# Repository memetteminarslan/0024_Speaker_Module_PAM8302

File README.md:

# 0024_Speaker_Module_PAM8302
You are seeing a large number of widely used Speaker Module in electronic development kits. More information coming soon...

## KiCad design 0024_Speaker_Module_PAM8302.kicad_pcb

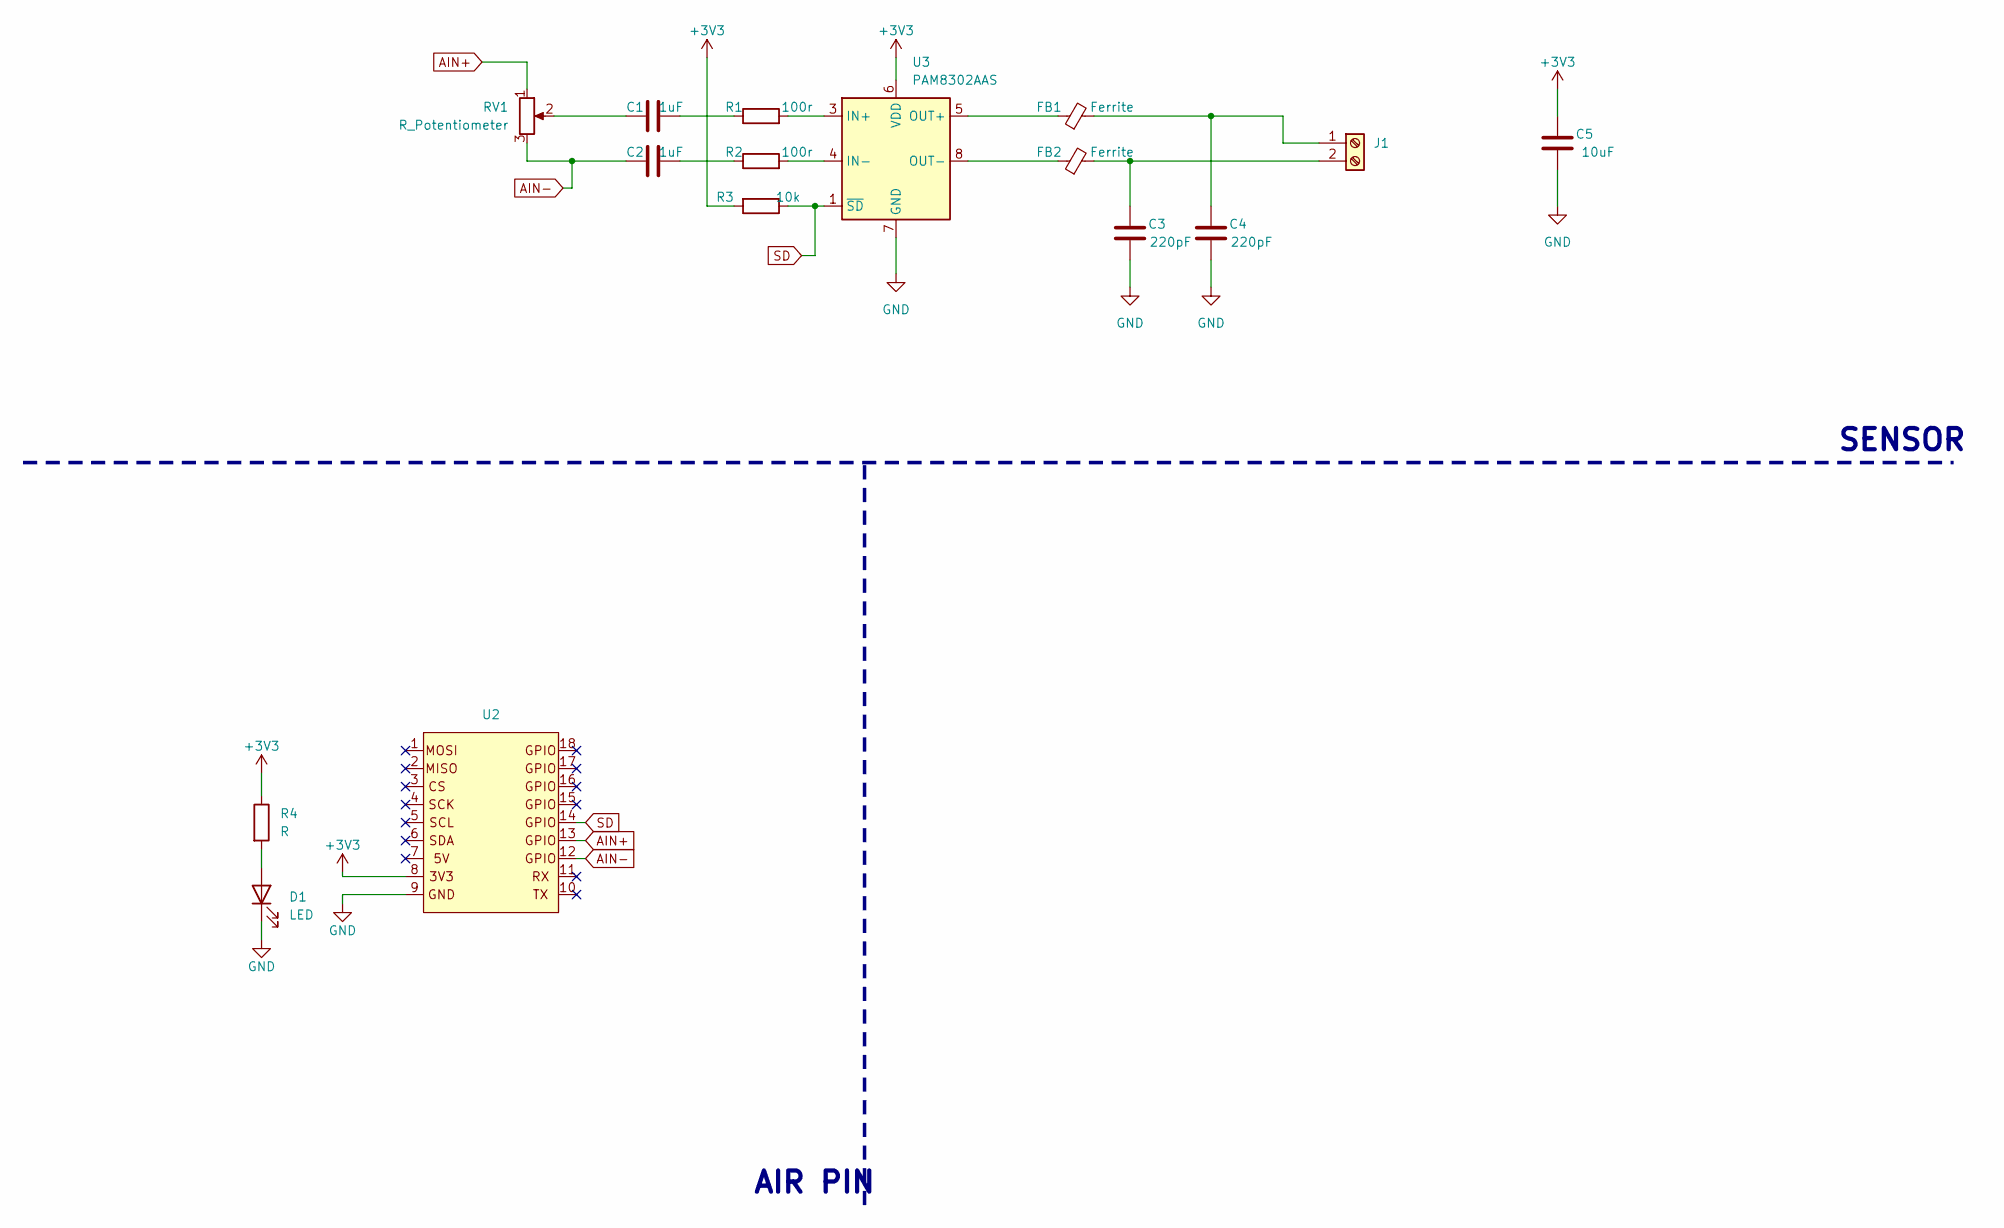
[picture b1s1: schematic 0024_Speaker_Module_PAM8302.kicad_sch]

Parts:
C1, C2: 1uF; C_0805_2012Metric
C3, C4: 220pF; C_0805_2012Metric
C5: 10uF; C_0603_1608Metric
D1: LED; LED_0805_2012Metric
FB1, FB2: Ferrite; L_0805_2012Metric
J1: Screw_Terminal_01x02; TerminalBlock_Phoenix_MKDS-1,5-2-5.08_1x02_P5.08mm_Horizont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
R1, R2: 100r; R_0805_2012Metric
R3: 10k; R_0805_2012Metric
R4: R; R_0805_2012Metric
RV1: R_Potentiometer; 3362P_1
U2: pin_header
U3: PAM8302AAS; MSOP-8_3x3mm_P0.65mm

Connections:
+3V3: C5.2, R3.2, R4.1, U2.8, U3.6 (VDD)
AIN+: RV1.1, U2.13
AIN-: C2.1, RV1.3, U2.12
GND: C3.1, C4.1, C5.1, D1.1 (K), U2.9, U3.7 (GND)
unnamed: C1.1, RV1.2
unnamed: C1.2, R1.1
unnamed: C2.2, R2.1
unnamed: D1.2 (A), R4.2
unnamed: C4.2, FB1.2, J1.1
unnamed: C3.2, FB2.2, J1.2
unnamed: R1.2, U3.3 (IN+)
unnamed: R2.2, U3.4 (IN-)
unnamed: FB1.1, U3.5 (OUT+)
unnamed: FB2.1, U3.8 (OUT-)
SD: R3.1, U2.14, U3.1 (~SD)

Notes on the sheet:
AIR PIN
SENSOR

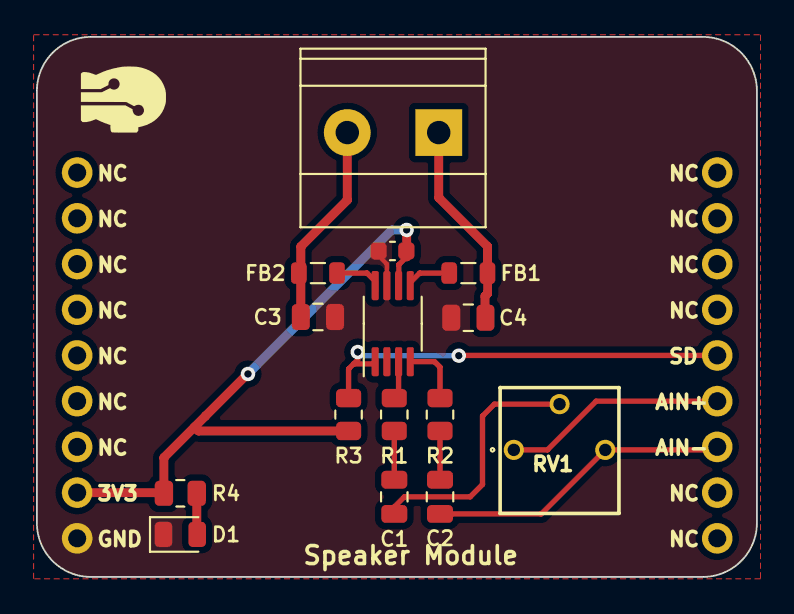
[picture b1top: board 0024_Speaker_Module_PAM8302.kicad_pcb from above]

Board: 2 copper layers, 40.0 x 30.0 mm, 16 parts (0 on the bottom side), 15 nets.
